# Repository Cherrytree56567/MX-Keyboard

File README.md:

# MX Keyboard
A Keyboard I made for Hackboard. It has a built-in USB C Hub and has Hotswap support.

## Info
 - 0.25mm Tolerance
 - Black Case

## Features
 - USB C Hub
 - RP2040
 - 61 Keys
 - Cherry MX Switches
 - Kailh Hotswap Sockets

# CAD
Here are some photos of the CAD 3D Print. It uses M2 Threads that are 6mm long on the top (gray part) and a 1.6mm M2 nut on the bottom plate (blue part) to raise the pcb.
I made the USB-C input and output separate so that they won't be confused and I've used Durock V3 Stabilizers for the spacebar, enter and shift keys. When I made my mini
keyboard last time, I made the holes too tight, so when I soldered the keys, if it was slightly tilted, it wouldn't fit in the case. This time, I added a 1.5mm padding.
<br><br>

Here is a photo of pcb and the case put together without the keys.<br><br>

# PCB
Here are some photos of the PCB. I've made most of the main components to sit on the top, to prevent electromagnetic interference, and I've also uses ground fills.
The diodes and Kailh Hotswap sockets are placed under the board. The Git Repo was pretty messy because I had multiple revisions of the pcb and the case and I didn't
update some parts like the readme. It should be organised now. The wiring was pretty hard becuase it was my first time making a keyboard. I made a mini keyboard, but
there were some more things to worry about when making a full keyboard. I've used USB 2.0 because dealing with impedences was pretty difficult, and I didn't need a
USB 3.0 port anyway. If you want to take an upclose look at the pcb or the schematic, you can look the pdf's on the root of this repo.

# Firmware
Unfortunatly, I don't know if the code works, because I haven't gotten the PCB yet, but to install it:
 - Install Circuit Python
   - [Download CircuitPython](https://circuitpython.org/board/raspberry_pi_pico/)
   - Plug the Keyboard in
   - Drag the .uf2 into the RP2040 Drive
 - Install KMK
   - [Download KMK](https://github.com/KMKfw/kmk_firmware/archive/refs/heads/master.zip)
   - Unzip it and copy the `kmk` folder from `kmk_firmware-main` to the CIRCUITPY Drive
 - Install Firmware
   - Copy the Code from [src/main.py](https://github.com/Cherrytree56567/MX-Keyboard/raw/refs/heads/main/src/main.py)
   - Create a new file in the CIRCUITPY Drive called `code.py` and paste it in.

# Building
1. Print out the 3D Print and order the PCB
2. Solder all the parts on the PCB
3. Add the Kailh SMD Keys
4. Add the Durock V3 Stabilizers
5. Push the threads and nuts into the PCB using a Soldering Iron
6. Place the PCB in the case and screw it in
7. Install Firmware
<br>
Here is the JLC Ordering Screen

# Bill of Materials
> [!NOTE]
> All Prices are in USD

|Designator                                  |Footprint                                   |Quantity|Value                  |URL                                                       |Price_USD|
|--------------------------------------------|--------------------------------------------|--------|-----------------------|----------------------------------------------------------|---------|
|C1, C2                                      |0402                                        |2       |15p                    |https://www.lcsc.com/product-detail/C86285.html           |$0.36    |
|C10, C8                                     |0402                                        |2       |1u                     |https://www.lcsc.com/product-detail/C435415.html          |$0.73    |
|C11, C12, C13, C14, C15, C16, C5, C6, C7, C9|0402                                        |10      |100n                   |https://www.lcsc.com/product-detail/C131394.html          |$0.29    |
|C23, C24                                    |0805                                        |2       |10uF                   |https://www.lcsc.com/product-detail/C18185764.html        |$0.39    |
|C25                                         |0805                                        |1       |100nF                  |https://www.lcsc.com/product-detail/C53084519.html        |$0.29    |
|C3, C4                                      |0805                                        |2       |10u                    |https://www.lcsc.com/product-detail/C2167686.html         |$0.61    |
|D1, D...                                    |Diode_DO-35                                 |61      |Diode                  |https://www.lcsc.com/product-detail/C84410.html           |$1.72    |
|D34                                         |1206                                        |1       |MBR120VLSFT1G          |https://www.lcsc.com/product-detail/C223608.html          |$0.70    |
|J1, J2, J4, J5                              |USB_C_Receptacle_HRO_TYPE-C-31-M-12         |1       |USB_C_Receptacle_USB2.0|https://www.aliexpress.com/item/1005003285152827.html?mp=1|$4.01    |
|R1, R2                                      |0805                                        |2       |5.1K                   |https://www.lcsc.com/product-detail/C490833.html          |$0.76    |
|R14, R15, R16, R17, R18, R19                |0805                                        |6       |56K                    |https://www.lcsc.com/product-detail/C21571499.html        |$0.52    |
|R3, R5                                      |0402                                        |2       |1k                     |https://www.lcsc.com/product-detail/C852624.html          |$0.86    |
|R4                                          |0402                                        |1       |DNF                    |                                                          |$0       |
|R6, R7                                      |0402                                        |2       |27                     |https://www.aliexpress.com/item/1005005433144951.html?mp=1|$2.46    |
|S1                                          |MX_PCB_1.00u                                |65      |Key                    |https://www.aliexpress.com/item/1005003944834891.html?mp=1|$19.06   |
|SW1                                         |SW_Push_1P1T_NO_Vertical_Wuerth_434133025816|1       |SW_Push                |https://www.lcsc.com/product-detail/C221897.html          |$0.49    |
|U1                                          |SOIC-16_4.55x10.3mm_P1.27mm                 |1       |SL2.1A                 |https://www.aliexpress.com/item/1005005552905296.html?mp=1|$2.33    |
|U2                                          |SOT-223-3_TabPin2                           |1       |NCP1117-3.3_SOT223     |https://www.lcsc.com/product-detail/C26537.html           |$1.31    |
|U3                                          |SOIC-8_5.23x5.23mm_P1.27mm                  |1       |W25Q128JVS             |https://www.aliexpress.com/item/1005008022185475.html     |$4.88    |
|U4                                          |RP2040-QFN-56                               |1       |RP2040                 |https://www.lcsc.com/product-detail/C2040.html            |$0.95    |
|Y1                                          |Crystal_SMD_3225-4Pin_3.2x2.5mm             |1       |ABM8-272-T3            |https://www.lcsc.com/product-detail/C20625731.html        |$1.45    |
|N/A                                         |Standoff                                    |4       |M2X6                   |https://www.aliexpress.com/item/1005008551732587.html     |$2.04    |
|N/A                                         |Nut                                         |12      |Nut                    |https://www.aliexpress.com/item/1005008755211193.html     |$3.04    |
|N/A                                         |Screw                                       |5       |M2_10mm                |https://www.ebay.com.au/itm/363744921549?var=632961986863 |$2.26    |
|N/A                                         |Socket                                      |70      |Kailh                  |https://www.aliexpress.com/item/1005007225352311.html?mp=1|$0.99    |
|N/A                                         |Stabilizer                                  |1       |Durock_V3_Stabilizers  |https://www.aliexpress.com/item/1005006628741999.html?mp=1|$15.56   |
|N/A                                         |Key_Caps                                    |1       |Black_Line_131         |https://www.aliexpress.com/item/1005007016258336.html?mp=1|$24.62   |
|N/A                                         |PCB                                         |1       |JLC_PCB                |https://jlcpcb.com/                                       |$18.40   |
|N/A                                         |JLCPCB Shipping                             |1       |JLCPCB_Shipping        |https://www.jlcpcb.com                                    |$12.73   |
|N/A                                         |Aliexpress Tax                              |1       |ALIEXPRESS_TAX         |https://www.aliexpress.com                                |$8.26    |
|N/A                                         |LCSC Shipping                               |1       |LCSC_Shipping          |https://www.lcsc.com                                      |$12.81   |

Total Price: US$142.65

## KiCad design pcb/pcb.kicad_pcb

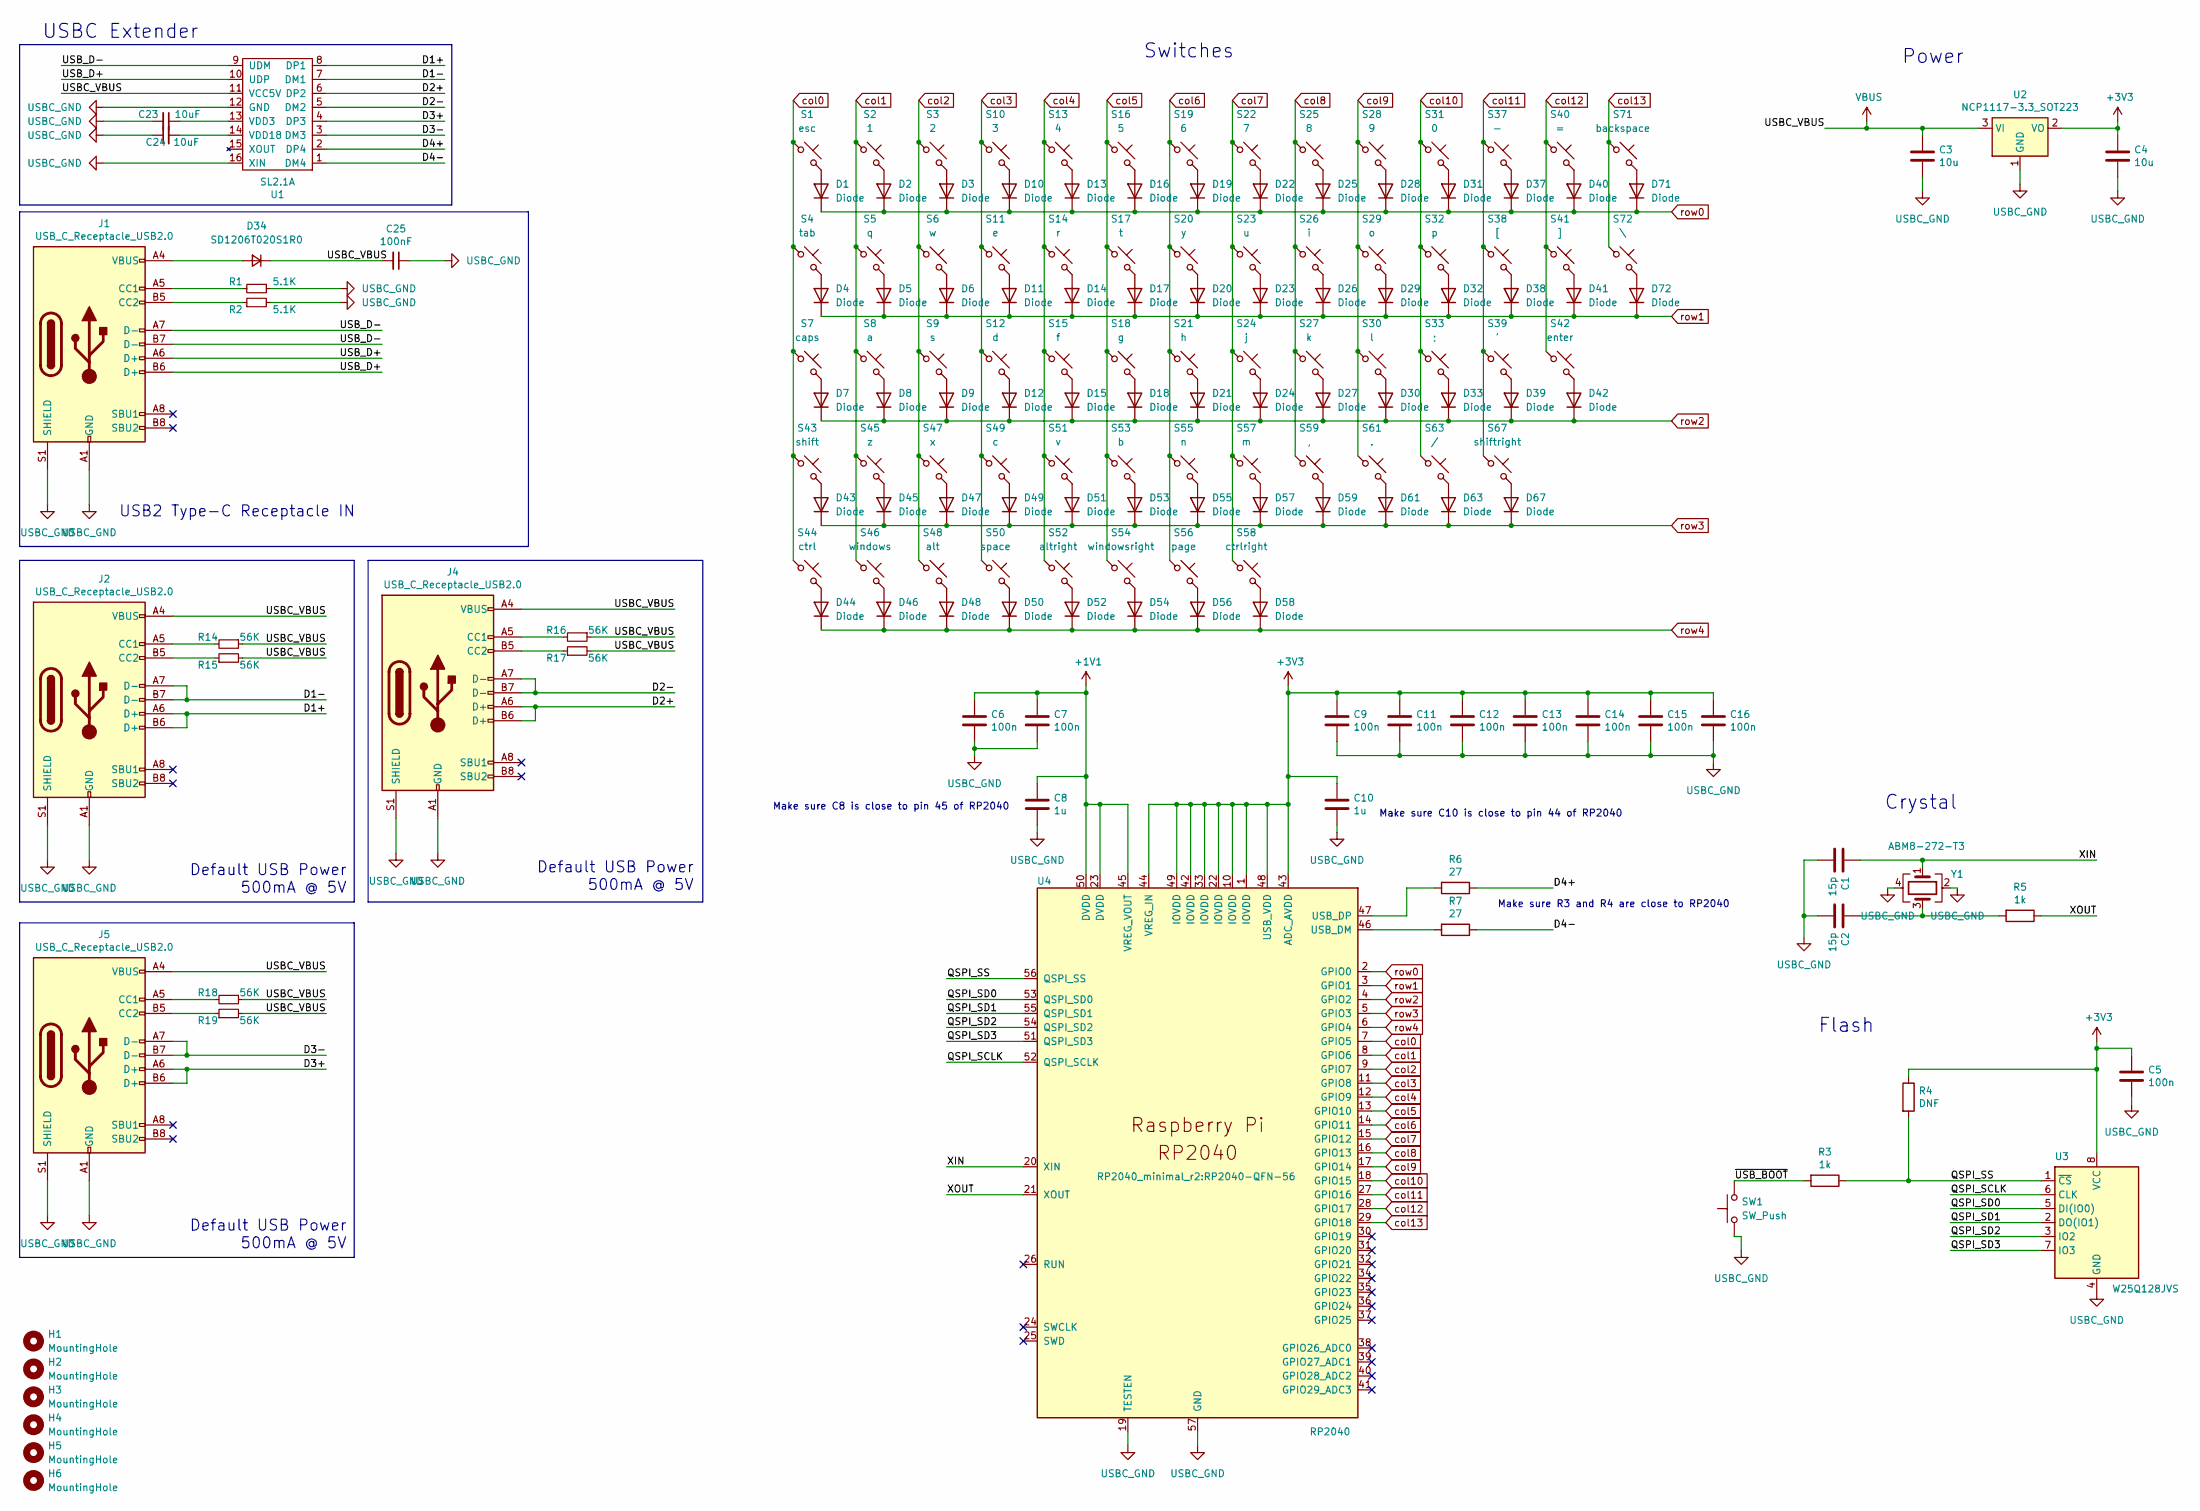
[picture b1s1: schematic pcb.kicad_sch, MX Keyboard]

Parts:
C1, C2: 15p; C_0402_1005Metric
C3, C4: 10u; C_0805_2012Metric
C5, C6, C7, C9, C11, C12, C13, C14, C15, C16: 100n; C_0402_1005Metric
C8, C10: 1u; C_0402_1005Metric
C23, C24: 10uF; C_0805_2012Metric_Pad1.18x1.45mm_HandSolder
C25: 100nF; C_0805_2012Metric_Pad1.18x1.45mm_HandSolder
D1, D2, D3, D4, D5, D6, D7, D8, D9, D10, D11, D12, D13, D14, D15, D16, D17, D18, D19, D20, D21, D22, D23, D24, D25, D26, D27, D28, D29, D30, D31, D32, D33, D37, D38, D39, D40, D41, D42, D43, D44, D45, D46, D47, D48, D49, D50, D51, D52, D53, D54, D55, D56, D57, D58, D59, D61, D63, D67, D71, D72: Diode; Diode_DO-35
D34: SD1206T020S1R0; D_1206_3216Metric_Pad1.42x1.75mm_HandSolder
H1, H2, H3, H4, H5, H6: MountingHole; MountingHole_2.1mm
J1, J2, J4, J5: USB_C_Receptacle_USB2.0; USB_C_Receptacle_HRO_TYPE-C-31-M-12
R1, R2: 5.1K; R_0805_2012Metric_Pad1.20x1.40mm_HandSolder
R3, R5: 1k; R_0402_1005Metric
R4: DNF; R_0402_1005Metric
R6, R7: 27; R_0402_1005Metric
R14, R15, R16, R17, R18, R19: 56K; R_0805_2012Metric_Pad1.20x1.40mm_HandSolder
S1: esc; SW_Hotswap_Kailh_MX_1.00u
S2: 1; SW_Hotswap_Kailh_MX_1.00u
S3: 2; SW_Hotswap_Kailh_MX_1.00u
S4: tab; SW_Hotswap_Kailh_MX_1.00u
S5: q; SW_Hotswap_Kailh_MX_1.00u
S6: w; SW_Hotswap_Kailh_MX_1.00u
S7: caps; SW_Hotswap_Kailh_MX_1.00u
S8: a; SW_Hotswap_Kailh_MX_1.00u
S9: s; SW_Hotswap_Kailh_MX_1.00u
S10: 3; SW_Hotswap_Kailh_MX_1.00u
S11: e; SW_Hotswap_Kailh_MX_1.00u
S12: d; SW_Hotswap_Kailh_MX_1.00u
S13: 4; SW_Hotswap_Kailh_MX_1.00u
S14: r; SW_Hotswap_Kailh_MX_1.00u
S15: f; SW_Hotswap_Kailh_MX_1.00u
S16: 5; SW_Hotswap_Kailh_MX_1.00u
S17: t; SW_Hotswap_Kailh_MX_1.00u
S18: g; SW_Hotswap_Kailh_MX_1.00u
S19: 6; SW_Hotswap_Kailh_MX_1.00u
S20: y; SW_Hotswap_Kailh_MX_1.00u
S21: h; SW_Hotswap_Kailh_MX_1.00u
S22: 7; SW_Hotswap_Kailh_MX_1.00u
S23: u; SW_Hotswap_Kailh_MX_1.00u
S24: j; SW_Hotswap_Kailh_MX_1.00u
S25: 8; SW_Hotswap_Kailh_MX_1.00u
S26: i; SW_Hotswap_Kailh_MX_1.00u
S27: k; SW_Hotswap_Kailh_MX_1.00u
S28: 9; SW_Hotswap_Kailh_MX_1.00u
S29: o; SW_Hotswap_Kailh_MX_1.00u
S30: l; SW_Hotswap_Kailh_MX_1.00u
S31: 0; SW_Hotswap_Kailh_MX_1.00u
S32: p; SW_Hotswap_Kailh_MX_1.00u
S33: ;; SW_Hotswap_Kailh_MX_1.00u
S37: -; SW_Hotswap_Kailh_MX_1.00u
S38: [; SW_Hotswap_Kailh_MX_1.00u
S39: '; SW_Hotswap_Kailh_MX_1.00u
S40: =; SW_Hotswap_Kailh_MX_1.00u
S41: ]; SW_Hotswap_Kailh_MX_1.00u
S42: enter; SW_Hotswap_Kailh_MX_2.25u
S43: shift; SW_Hotswap_Kailh_MX_2.00u
S44: ctrl; SW_Hotswap_Kailh_MX_1.25u
S45: z; SW_Hotswap_Kailh_MX_1.00u
S46: windows; SW_Hotswap_Kailh_MX_1.25u
S47: x; SW_Hotswap_Kailh_MX_1.00u
S48: alt; SW_Hotswap_Kailh_MX_1.25u
S49: c; SW_Hotswap_Kailh_MX_1.00u
S50: space; SW_Hotswap_Kailh_MX_6.25u
S51: v; SW_Hotswap_Kailh_MX_1.00u
S52: altright; SW_Hotswap_Kailh_MX_1.25u
S53: b; SW_Hotswap_Kailh_MX_1.00u
S54: windowsright; SW_Hotswap_Kailh_MX_1.25u
S55: n; SW_Hotswap_Kailh_MX_1.00u
S56: page; SW_Hotswap_Kailh_MX_1.00u
S57: m; SW_Hotswap_Kailh_MX_1.00u
S58: ctrlright; SW_Hotswap_Kailh_MX_1.25u
S59: ,; SW_Hotswap_Kailh_MX_1.00u
S61: .; SW_Hotswap_Kailh_MX_1.00u
S63: /; SW_Hotswap_Kailh_MX_1.00u
S67: shiftright; SW_Hotswap_Kailh_MX_2.75u
S71: backspace; SW_Hotswap_Kailh_MX_1.75u
S72: \; SW_Hotswap_Kailh_MX_1.25u
SW1: SW_Push; SW_Push_1P1T_NO_Vertical_Wuerth_434133025816
U1: SL2.1A; SOIC-16_4.55x10.3mm_P1.27mm
U2: NCP1117-3.3_SOT223; SOT-223-3_TabPin2
U3: W25Q128JVS; SOIC-8_5.3x5.3mm_P1.27mm
U4: RP2040; RP2040-QFN-56
Y1: ABM8-272-T3; Crystal_SMD_3225-4Pin_3.2x2.5mm

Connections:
+1V1: C6.1, C7.1, C8.1, U4.23 (DVDD), U4.45 (VREG_VOUT), U4.50 (DVDD)
+3V3: C4.1, C5.1, C9.1, C10.1, C11.1, C12.1, C13.1, C14.1, C15.1, C16.1, R4.1, U2.2 (VO), U3.8 (VCC), U4.1 (IOVDD), U4.10 (IOVDD), U4.22 (IOVDD), U4.33 (IOVDD), U4.42 (IOVDD), U4.43 (ADC_AVDD), U4.44 (VREG_IN), U4.48 (USB_VDD), U4.49 (IOVDD)
/D1+: J2.A6 (D+), J2.B6 (D+), U1.8 (DP1)
/D1-: J2.A7 (D-), J2.B7 (D-), U1.7 (DM1)
/D2+: J4.A6 (D+), J4.B6 (D+), U1.6 (DP2)
/D2-: J4.A7 (D-), J4.B7 (D-), U1.5 (DM2)
/D3+: J5.A6 (D+), J5.B6 (D+), U1.4 (DP3)
/D3-: J5.A7 (D-), J5.B7 (D-), U1.3 (DM3)
/D4+: R6.1, U1.2 (DP4)
/D4-: R7.1, U1.1 (DM4)
/QSPI_SCLK: U3.6 (CLK), U4.52 (QSPI_SCLK)
/QSPI_SD0: U3.5 (DI(IO0)), U4.53 (QSPI_SD0)
/QSPI_SD1: U3.2 (DO(IO1)), U4.55 (QSPI_SD1)
/QSPI_SD2: U3.3 (IO2), U4.54 (QSPI_SD2)
/QSPI_SD3: U3.7 (IO3), U4.51 (QSPI_SD3)
/QSPI_SS: R3.1, R4.2, U3.1 (~CS), U4.56 (QSPI_SS)
/USB_D+: J1.A6 (D+), J1.B6 (D+), U1.10 (UDP)
/USB_D-: J1.A7 (D-), J1.B7 (D-), U1.9 (UDM)
/XIN: C1.1, U4.20 (XIN), Y1.1
/XOUT: R5.1, U4.21 (XOUT)
/~USB_BOOT: R3.2, SW1.2
unnamed: C2.1, R5.2, Y1.3
unnamed: D1.2 (A), S1.2
unnamed: D2.2 (A), S2.2
unnamed: D3.2 (A), S3.2
unnamed: D4.2 (A), S4.2
unnamed: D5.2 (A), S5.2
unnamed: D6.2 (A), S6.2
unnamed: D7.2 (A), S7.2
unnamed: D8.2 (A), S8.2
unnamed: D9.2 (A), S9.2
unnamed: D10.2 (A), S10.2
unnamed: D11.2 (A), S11.2
unnamed: D12.2 (A), S12.2
unnamed: D13.2 (A), S13.2
unnamed: D14.2 (A), S14.2
unnamed: D15.2 (A), S15.2
unnamed: D16.2 (A), S16.2
unnamed: D17.2 (A), S17.2
unnamed: D18.2 (A), S18.2
unnamed: D19.2 (A), S19.2
unnamed: D20.2 (A), S20.2
unnamed: D21.2 (A), S21.2
unnamed: D22.2 (A), S22.2
unnamed: D23.2 (A), S23.2
unnamed: D24.2 (A), S24.2
unnamed: D25.2 (A), S25.2
unnamed: D26.2 (A), S26.2
unnamed: D27.2 (A), S27.2
unnamed: D28.2 (A), S28.2
unnamed: D29.2 (A), S29.2
unnamed: D30.2 (A), S30.2
unnamed: D31.2 (A), S31.2
unnamed: D32.2 (A), S32.2
unnamed: D33.2 (A), S33.2
unnamed: D34.2 (A), J1.A4 (VBUS), J1.A9 (VBUS), J1.B4 (VBUS), J1.B9 (VBUS)
unnamed: D37.2 (A), S37.2
unnamed: D38.2 (A), S38.2
unnamed: D39.2 (A), S39.2
unnamed: D40.2 (A), S40.2
unnamed: D41.2 (A), S41.2
unnamed: D42.2 (A), S42.2
unnamed: D43.2 (A), S43.2
unnamed: D44.2 (A), S44.2
unnamed: D45.2 (A), S45.2
unnamed: D46.2 (A), S46.2
unnamed: D47.2 (A), S47.2
unnamed: D48.2 (A), S48.2
unnamed: D49.2 (A), S49.2
unnamed: D50.2 (A), S50.2
unnamed: D51.2 (A), S51.2
unnamed: D52.2 (A), S52.2
unnamed: D53.2 (A), S53.2
unnamed: D54.2 (A), S54.2
unnamed: D55.2 (A), S55.2
unnamed: D56.2 (A), S56.2
unnamed: D57.2 (A), S57.2
unnamed: D58.2 (A), S58.2
unnamed: D59.2 (A), S59.2
unnamed: D61.2 (A), S61.2
unnamed: D63.2 (A), S63.2
unnamed: D67.2 (A), S67.2
unnamed: D71.2 (A), S71.2
unnamed: D72.2 (A), S72.2
unnamed: J1.A5 (CC1), R1.2
unnamed: J1.B5 (CC2), R2.1
unnamed: J2.A5 (CC1), R14.2
unnamed: J2.B5 (CC2), R15.1
unnamed: J4.A5 (CC1), R16.2
unnamed: J4.B5 (CC2), R17.1
unnamed: J5.A5 (CC1), R18.2
unnamed: J5.B5 (CC2), R19.1
unnamed: C23.1, U1.13 (VDD3)
unnamed: C24.2, U1.14 (VDD18)
unnamed: R7.2, U4.46 (USB_DM)
unnamed: R6.2, U4.47 (USB_DP)
USBC_GND: C1.2, C2.2, C3.2, C4.2, C5.2, C6.2, C7.2, C8.2, C9.2, C10.2, C11.2, C12.2, C13.2, C14.2, C15.2, C16.2, C23.2, C24.1, C25.1, J1.A1 (GND), J1.A12 (GND), J1.B1 (GND), J1.B12 (GND), J1.S1 (SHIELD), J2.A1 (GND), J2.A12 (GND), J2.B1 (GND), J2.B12 (GND), J2.S1 (SHIELD), J4.A1 (GND), J4.A12 (GND), J4.B1 (GND), J4.B12 (GND), J4.S1 (SHIELD), J5.A1 (GND), J5.A12 (GND), J5.B1 (GND), J5.B12 (GND), J5.S1 (SHIELD), R1.1, R2.2, SW1.1, U1.12 (GND), U1.16 (XIN), U2.1 (GND), U3.4 (GND), U4.19 (TESTEN), U4.57 (GND), Y1.2, Y1.4
VBUS: C3.1, C25.2, D34.1 (K), J2.A4 (VBUS), J2.A9 (VBUS), J2.B4 (VBUS), J2.B9 (VBUS), J4.A4 (VBUS), J4.A9 (VBUS), J4.B4 (VBUS), J4.B9 (VBUS), J5.A4 (VBUS), J5.A9 (VBUS), J5.B4 (VBUS), J5.B9 (VBUS), R14.1, R15.2, R16.1, R17.2, R18.1, R19.2, U1.11 (VCC5V), U2.3 (VI)
col0: S1.1, S4.1, S7.1, S43.1, S44.1, U4.7 (GPIO5)
col1: S2.1, S5.1, S8.1, S45.1, S46.1, U4.8 (GPIO6)
col2: S3.1, S6.1, S9.1, S47.1, S48.1, U4.9 (GPIO7)
col3: S10.1, S11.1, S12.1, S49.1, S50.1, U4.11 (GPIO8)
col4: S13.1, S14.1, S15.1, S51.1, S52.1, U4.12 (GPIO9)
col5: S16.1, S17.1, S18.1, S53.1, S54.1, U4.13 (GPIO10)
col6: S19.1, S20.1, S21.1, S55.1, S56.1, U4.14 (GPIO11)
col7: S22.1, S23.1, S24.1, S57.1, S58.1, U4.15 (GPIO12)
col8: S25.1, S26.1, S27.1, S59.1, U4.16 (GPIO13)
col9: S28.1, S29.1, S30.1, S61.1, U4.17 (GPIO14)
col10: S31.1, S32.1, S33.1, S63.1, U4.18 (GPIO15)
col11: S37.1, S38.1, S39.1, S67.1, U4.27 (GPIO16)
col12: S40.1, S41.1, S42.1, U4.28 (GPIO17)
col13: S71.1, S72.1, U4.29 (GPIO18)
row0: D1.1 (K), D2.1 (K), D3.1 (K), D10.1 (K), D13.1 (K), D16.1 (K), D19.1 (K), D22.1 (K), D25.1 (K), D28.1 (K), D31.1 (K), D37.1 (K), D40.1 (K), D71.1 (K), U4.2 (GPIO0)
row1: D4.1 (K), D5.1 (K), D6.1 (K), D11.1 (K), D14.1 (K), D17.1 (K), D20.1 (K), D23.1 (K), D26.1 (K), D29.1 (K), D32.1 (K), D38.1 (K), D41.1 (K), D72.1 (K), U4.3 (GPIO1)
row2: D7.1 (K), D8.1 (K), D9.1 (K), D12.1 (K), D15.1 (K), D18.1 (K), D21.1 (K), D24.1 (K), D27.1 (K), D30.1 (K), D33.1 (K), D39.1 (K), D42.1 (K), U4.4 (GPIO2)
row3: D43.1 (K), D45.1 (K), D47.1 (K), D49.1 (K), D51.1 (K), D53.1 (K), D55.1 (K), D57.1 (K), D59.1 (K), D61.1 (K), D63.1 (K), D67.1 (K), U4.5 (GPIO3)
row4: D44.1 (K), D46.1 (K), D48.1 (K), D50.1 (K), D52.1 (K), D54.1 (K), D56.1 (K), D58.1 (K), U4.6 (GPIO4)

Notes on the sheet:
Make sure C8 is close to pin 45 of RP2040
Default USB Power 500mA @ 5V
Make sure C10 is close to pin 44 of RP2040
USBC Extender
Switches
Make sure R3 and R4 are close to RP2040
Flash
Power
USB2 Type-C Receptacle IN
Crystal

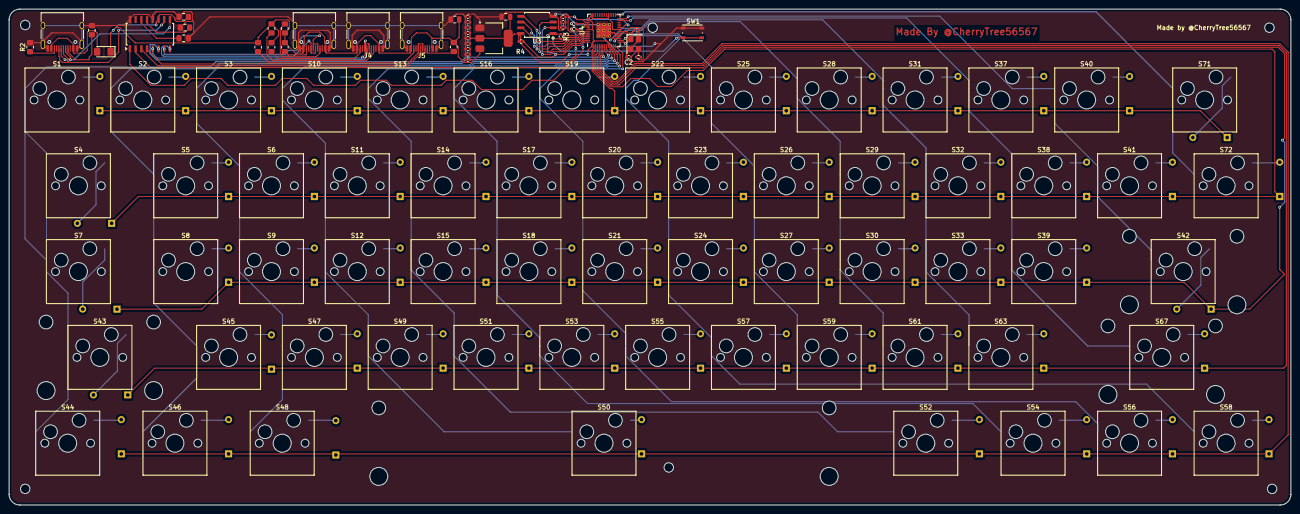
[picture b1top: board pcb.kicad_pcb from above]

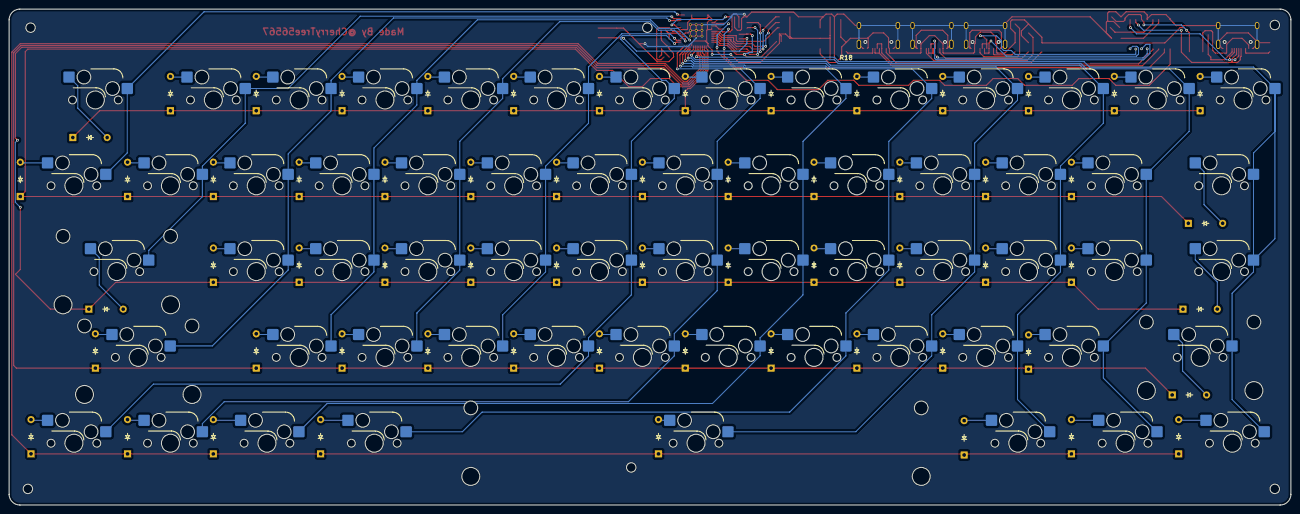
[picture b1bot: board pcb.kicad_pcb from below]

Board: 2 copper layers, 284.6 x 110.1 mm, 171 parts (61 on the bottom side), 117 nets.

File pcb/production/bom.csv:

Designator,Footprint,Quantity,Value,LCSC Part #
"C1, C2",0402,2,15p,
"C10, C8",0402,2,1u,
"C11, C12, C13, C14, C15, C16, C5, C6, C7, C9",0402,10,100n,
"C23, C24",0805,2,10uF,
C25,0805,1,100nF,
"C3, C4",0805,2,10u,
"D1, D10, D11, D12, D13, D14, D15, D16, D17, D18, D19, D2, D20, D21, D22, D23, D24, D25, D26, D27, D28, D29, D3, D30, D31, D32, D33, D37, D38, D39, D4, D40, D41, D42, D43, D44, D45, D46, D47, D48, D49, D5, D50, D51, D52, D53, D54, D55, D56, D57, D58, D59, D6, D61, D63, D67, D7, D71, D72, D8, D9",Diode_DO-35,61,Diode,
D34,1206,1,SD1206T020S1R0,
"J1, J2, J4, J5",USB_C_Receptacle_HRO_TYPE-C-31-M-12,4,USB_C_Receptacle_USB2.0,
"R1, R2",0805,2,5.1K,
"R14, R15, R16, R17, R18, R19",0805,6,56K,
"R3, R5",0402,2,1k,
R4,0402,1,DNF,
"R6, R7",0402,2,27,
S1,SW_Hotswap_Kailh_MX_1.00u,1,esc,
S10,SW_Hotswap_Kailh_MX_1.00u,1,3,
S11,SW_Hotswap_Kailh_MX_1.00u,1,e,
S12,SW_Hotswap_Kailh_MX_1.00u,1,d,
S13,SW_Hotswap_Kailh_MX_1.00u,1,4,
S14,SW_Hotswap_Kailh_MX_1.00u,1,r,
S15,SW_Hotswap_Kailh_MX_1.00u,1,f,
S16,SW_Hotswap_Kailh_MX_1.00u,1,5,
S17,SW_Hotswap_Kailh_MX_1.00u,1,t,
S18,SW_Hotswap_Kailh_MX_1.00u,1,g,
S19,SW_Hotswap_Kailh_MX_1.00u,1,6,
S2,SW_Hotswap_Kailh_MX_1.00u,1,1,
S20,SW_Hotswap_Kailh_MX_1.00u,1,y,
S21,SW_Hotswap_Kailh_MX_1.00u,1,h,
S22,SW_Hotswap_Kailh_MX_1.00u,1,7,
S23,SW_Hotswap_Kailh_MX_1.00u,1,u,
S24,SW_Hotswap_Kailh_MX_1.00u,1,j,
S25,SW_Hotswap_Kailh_MX_1.00u,1,8,
S26,SW_Hotswap_Kailh_MX_1.00u,1,i,
S27,SW_Hotswap_Kailh_MX_1.00u,1,k,
S28,SW_Hotswap_Kailh_MX_1.00u,1,9,
S29,SW_Hotswap_Kailh_MX_1.00u,1,o,
S3,SW_Hotswap_Kailh_MX_1.00u,1,2,
S30,SW_Hotswap_Kailh_MX_1.00u,1,l,
S31,SW_Hotswap_Kailh_MX_1.00u,1,0,
S32,SW_Hotswap_Kailh_MX_1.00u,1,p,
S33,SW_Hotswap_Kailh_MX_1.00u,1,;,
S37,SW_Hotswap_Kailh_MX_1.00u,1,-,
S38,SW_Hotswap_Kailh_MX_1.00u,1,[,
S39,SW_Hotswap_Kailh_MX_1.00u,1,',
S4,SW_Hotswap_Kailh_MX_1.00u,1,tab,
S40,SW_Hotswap_Kailh_MX_1.00u,1,=,
S41,SW_Hotswap_Kailh_MX_1.00u,1,],
S42,SW_Hotswap_Kailh_MX_2.25u,1,enter,
S43,SW_Hotswap_Kailh_MX_2.00u,1,shift,
S44,SW_Hotswap_Kailh_MX_1.25u,1,ctrl,
S45,SW_Hotswap_Kailh_MX_1.00u,1,z,
S46,SW_Hotswap_Kailh_MX_1.25u,1,windows,
S47,SW_Hotswap_Kailh_MX_1.00u,1,x,
S48,SW_Hotswap_Kailh_MX_1.25u,1,alt,
S49,SW_Hotswap_Kailh_MX_1.00u,1,c,
S5,SW_Hotswap_Kailh_MX_1.00u,1,q,
S50,SW_Hotswap_Kailh_MX_6.25u,1,space,
S51,SW_Hotswap_Kailh_MX_1.00u,1,v,
S52,SW_Hotswap_Kailh_MX_1.25u,1,altright,
S53,SW_Hotswap_Kailh_MX_1.00u,1,b,
S54,SW_Hotswap_Kailh_MX_1.25u,1,windowsright,
S55,SW_Hotswap_Kailh_MX_1.00u,1,n,
S56,SW_Hotswap_Kailh_MX_1.00u,1,page,
S57,SW_Hotswap_Kailh_MX_1.00u,1,m,
S58,SW_Hotswap_Kailh_MX_1.25u,1,ctrlright,
S59,SW_Hotswap_Kailh_MX_1.00u,1,",",
S6,SW_Hotswap_Kailh_MX_1.00u,1,w,
S61,SW_Hotswap_Kailh_MX_1.00u,1,.,
S63,SW_Hotswap_Kailh_MX_1.00u,1,/,
S67,SW_Hotswap_Kailh_MX_2.75u,1,shiftright,
S7,SW_Hotswap_Kailh_MX_1.00u,1,caps,
S71,SW_Hotswap_Kailh_MX_1.75u,1,backspace,
S72,SW_Hotswap_Kailh_MX_1.25u,1,\,
S8,SW_Hotswap_Kailh_MX_1.00u,1,a,
S9,SW_Hotswap_Kailh_MX_1.00u,1,s,
SW1,SW_Push_1P1T_NO_Vertical_Wuerth_434133025816,1,SW_Push,
U1,SOIC-16_4.55x10.3mm_P1.27mm,1,SL2.1A,
U2,SOT-223-3_TabPin2,1,NCP1117-3.3_SOT223,
U3,SOIC-8_5.3x5.3mm_P1.27mm,1,W25Q128JVS,
U4,RP2040-QFN-56,1,RP2040,
Y1,Crystal_SMD_3225-4Pin_3.2x2.5mm,1,ABM8-272-T3,

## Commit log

2025-02-06 Init
2025-02-06 StepFiles
2025-02-06 Fab Toolkit
2025-02-08 curved pcb
2025-02-08 Added Mounting Holes
2025-02-10 Added Proper Support
2025-02-13 Added Case Parts
2025-02-20 Added BOM and animations
2025-03-16 Added Modifications
2025-03-19 Redesign
2025-10-24 Update switch type and replace an image in README
2025-10-24 Fixed 3D Case and noise
2025-10-26 Revise BOM with component URLs and cleanup
    Updated BOM to include URLs for components and removed unused entries.
2025-10-26 Fixed Traces
2025-10-26 Fixed Plate
2025-10-26 Add shipping entries to BOM CSV
2025-10-26 Fixes
2025-10-26 Add additional image to README
    Added a new image to the README for better visualization.
2025-10-26 Step
2026-02-08 Added Silkscreen Username
